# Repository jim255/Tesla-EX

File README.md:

# Tesla-EX
3 piece KiCad project for a flat Tesla coil
1- primary driver layer optonal resonancew tuner:
2- primary layer 2 sides, 5 turns/side 10 total:could be stacked, parallel or series
3- secondary layer 2 sides, 120 turns/side 240 total : connection point is center serface mount pad on top and bottom

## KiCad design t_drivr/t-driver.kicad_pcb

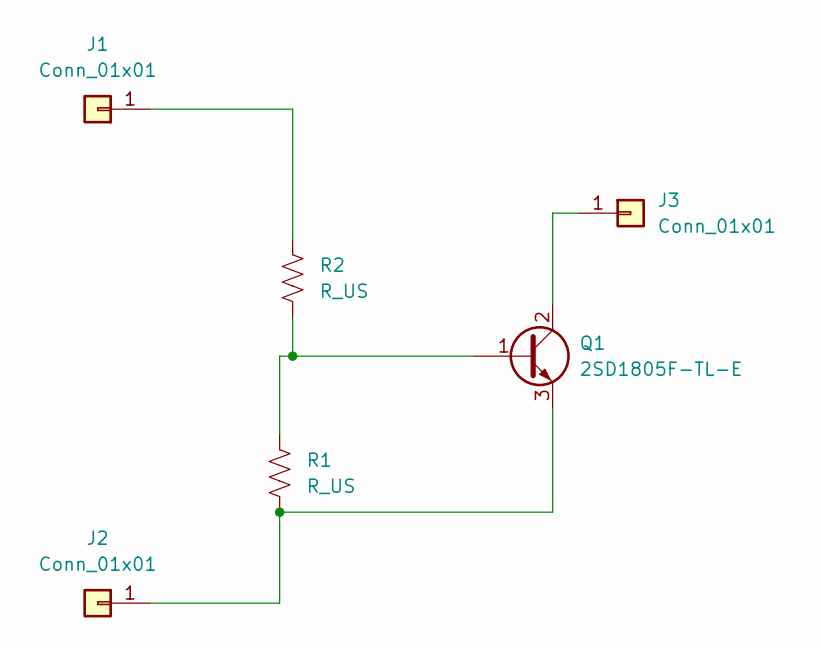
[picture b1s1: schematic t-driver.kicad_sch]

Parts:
J1, J2, J3: Conn_01x01; PinHeader_1x01_P2.54mm_Vertical
Q1: 2SD1805F-TL-E; TO-252-3_TabPin2
R1: R_US; R_1206_3216Metric_Pad1.30x1.75mm_HandSolder
R2: R_US; R_1210_3225Metric_Pad1.30x2.65mm_HandSolder

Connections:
unnamed: J1.1, R2.1
unnamed: J2.1, Q1.3 (E), R1.2
unnamed: J3.1, Q1.2 (C)
unnamed: Q1.1 (B), R1.1, R2.2

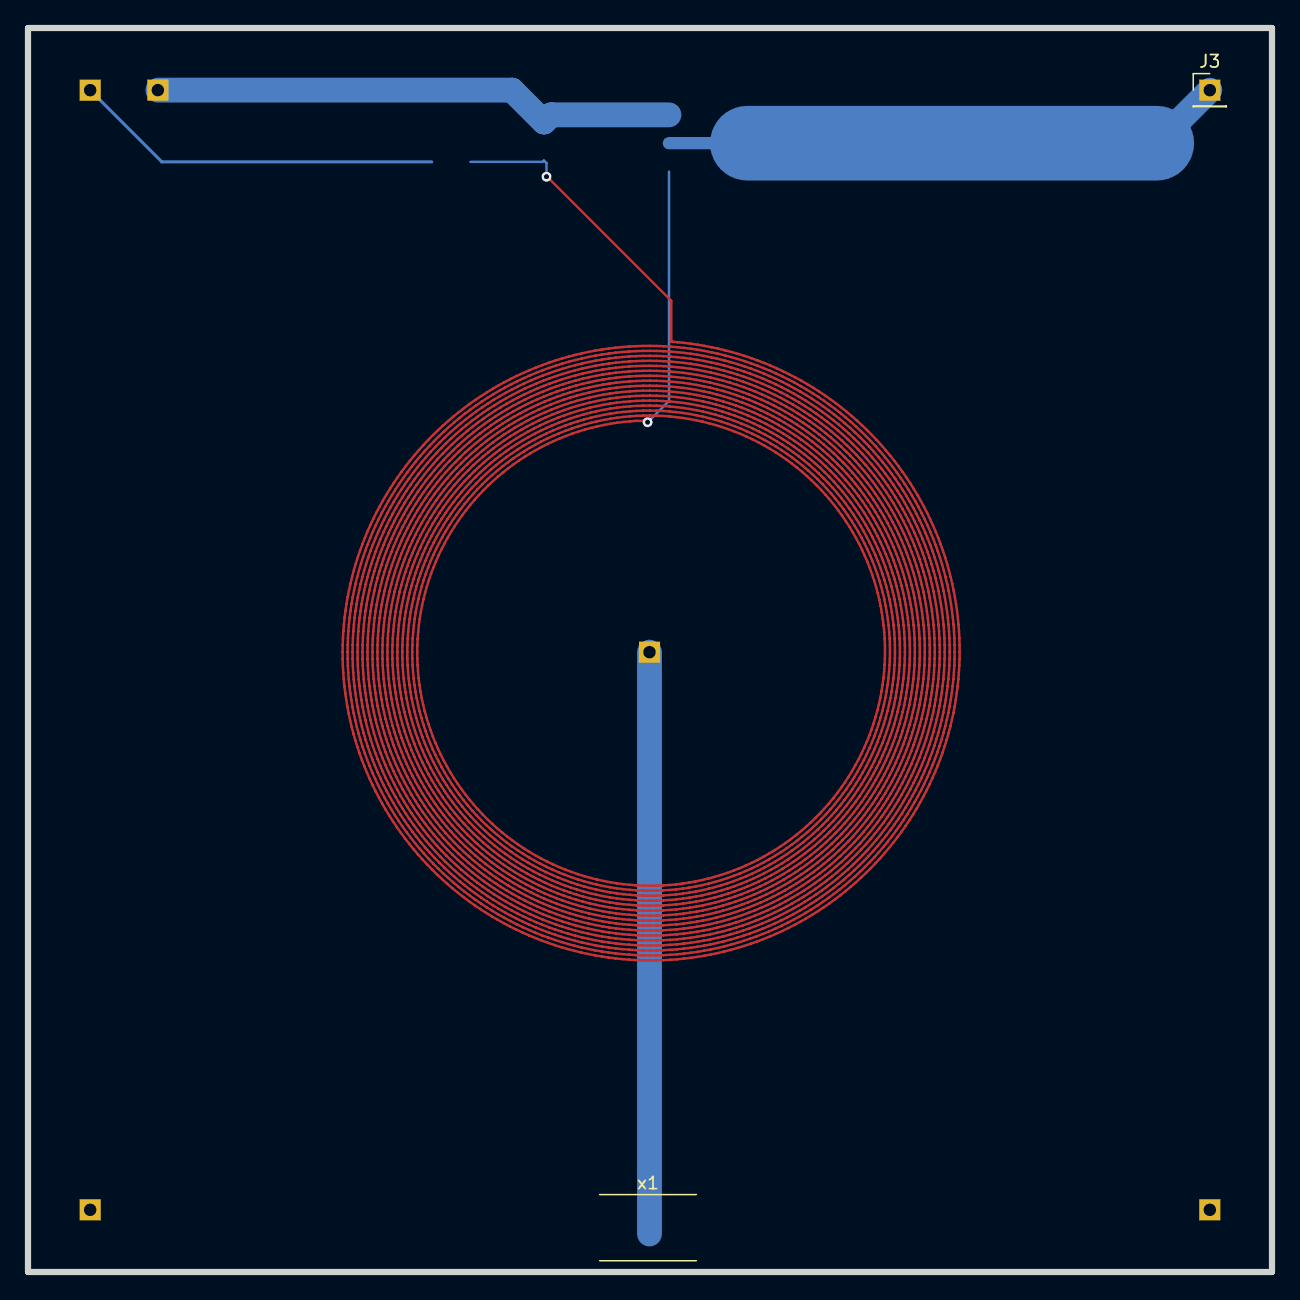
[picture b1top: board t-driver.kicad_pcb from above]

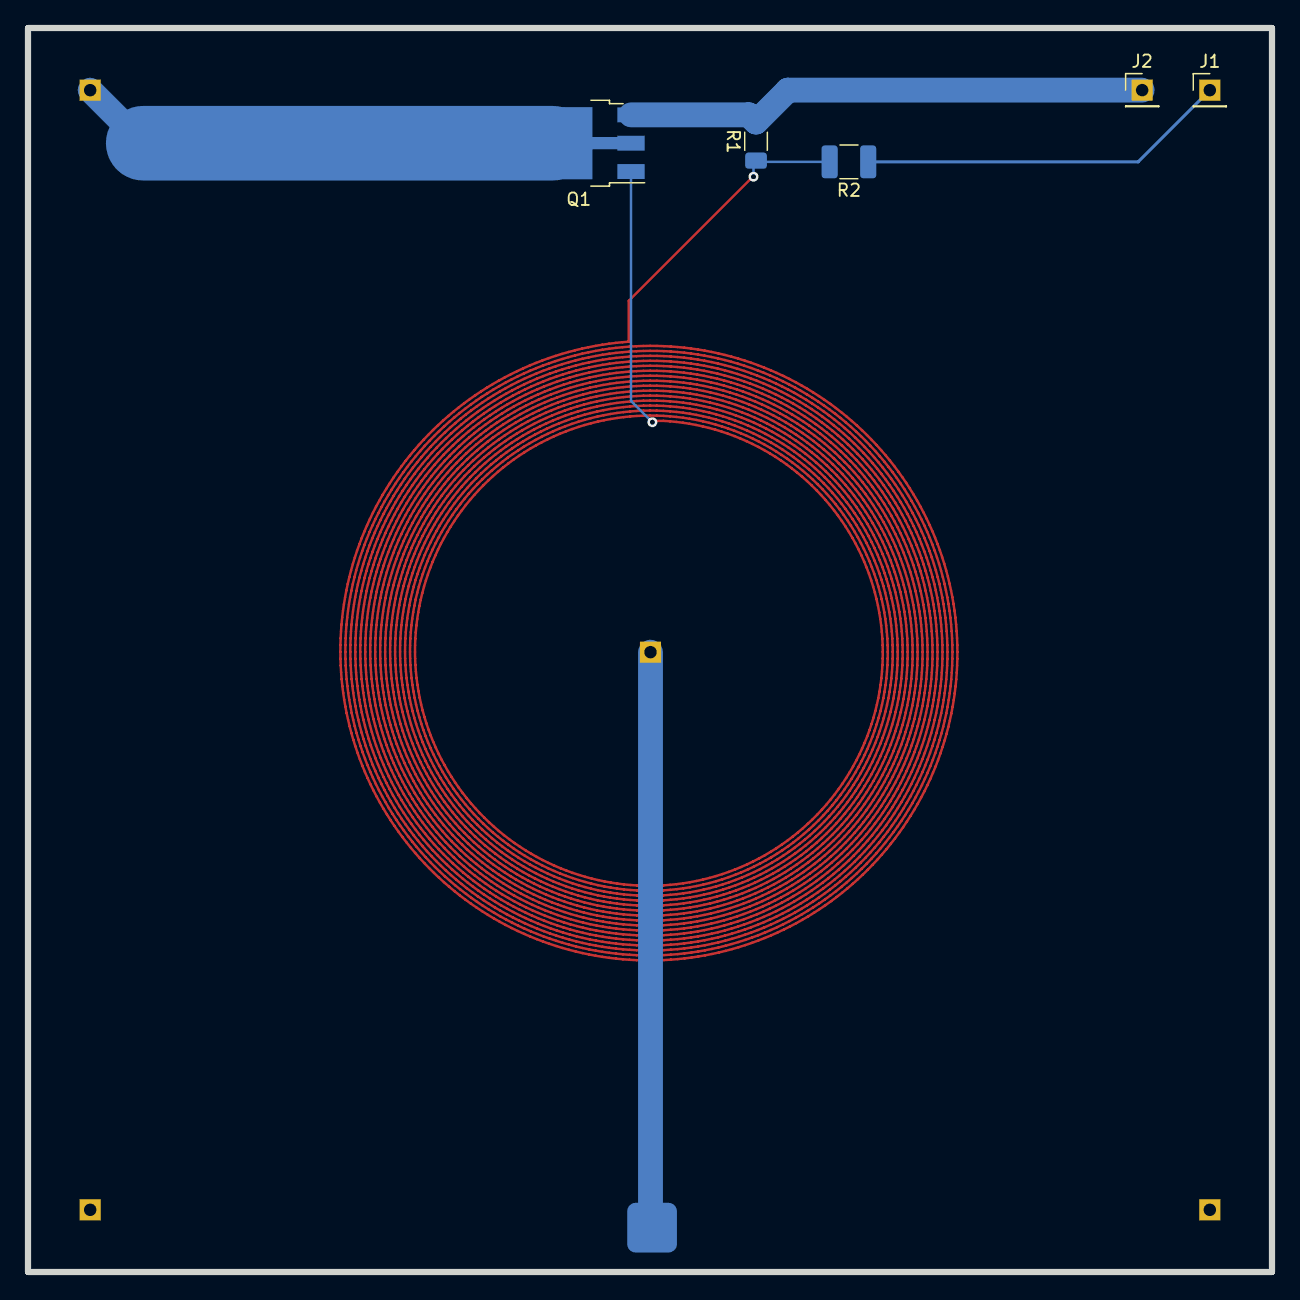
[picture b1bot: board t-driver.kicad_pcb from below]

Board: 2 copper layers, 100.0 x 100.0 mm, 7 parts (5 on the bottom side), 4 nets.

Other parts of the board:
x1: large_smx

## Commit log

2023-08-18 first release
    Added files for circuits and coils for first test set.
